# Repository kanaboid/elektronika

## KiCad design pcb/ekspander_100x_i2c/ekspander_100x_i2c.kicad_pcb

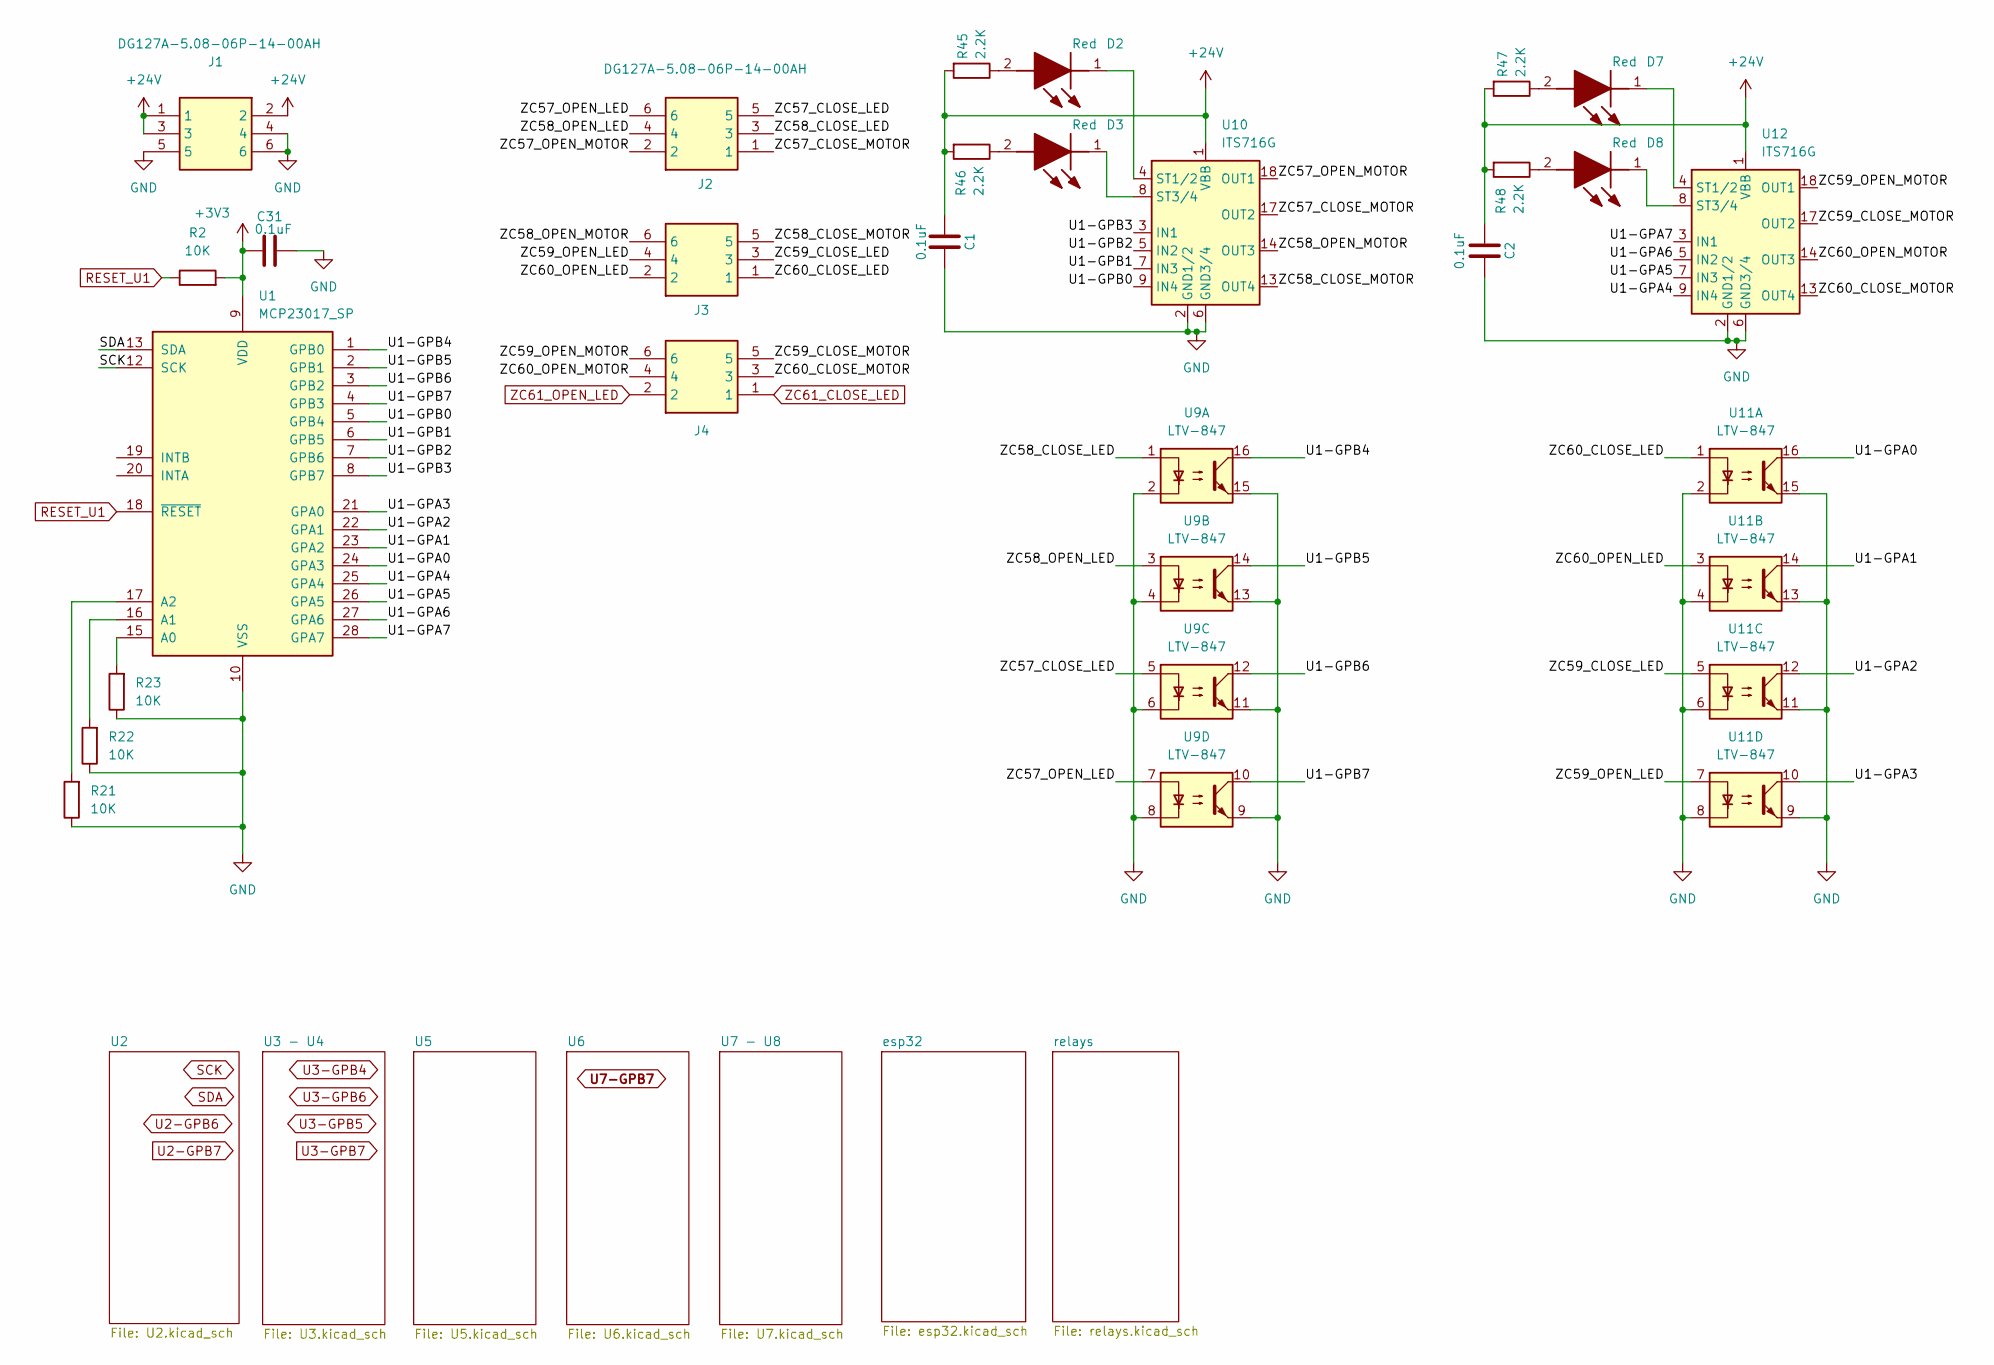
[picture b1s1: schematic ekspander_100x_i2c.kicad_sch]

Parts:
C1, C2, C31: 0.1uF; C_0805_2012Metric_Pad1.18x1.45mm_HandSolder
D2, D3, D7, D8: Red; LEDC2012X120N; Manufacturer_Part_Number LTST-C170KRKT; Mouser Part Number 859-LTST-C170KRKT
J1, J2, J3, J4: DG127A-5.08-06P-14-00AH; DG127A50806P1400AH; Manufacturer_Part_Number DG127A-5.08-06P-14-00AH
R2, R21, R22, R23: 10K; R_0805_2012Metric_Pad1.20x1.40mm_HandSolder
R45, R46, R47, R48: 2.2K; R_0805_2012Metric_Pad1.20x1.40mm_HandSolder
U1: MCP23017_SP; DIP-28_W7.62mm
U9, U11: LTV-847; DIP-16_W7.62mm
U10, U12: ITS716G; SOIC-20W_7.5x12.8mm_P1.27mm

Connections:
+3V3: C31.1, R2.2, U1.9 (VDD); also elsewhere on the board
+24V: C1.1, C2.1, J1.1, J1.2, J1.3, R45.2, R46.2, R47.2, R48.2, U10.1 (VBB), U10.10 (VBB), U10.11 (VBB), U10.12 (VBB), U10.15 (VBB), U10.16 (VBB), U10.19 (VBB), U10.20 (VBB), U12.1 (VBB), U12.10 (VBB), U12.11 (VBB), U12.12 (VBB), U12.15 (VBB), U12.16 (VBB), U12.19 (VBB), U12.20 (VBB); also elsewhere on the board
/U1-GPA0: U1.24 (GPA3), U11.16
/U1-GPA1: U1.23 (GPA2), U11.14
/U1-GPA2: U1.22 (GPA1), U11.12
/U1-GPA3: U1.21 (GPA0), U11.10
/U1-GPA4: U1.25 (GPA4), U12.9 (IN4)
/U1-GPA5: U1.26 (GPA5), U12.7 (IN3)
/U1-GPA6: U1.27 (GPA6), U12.5 (IN2)
/U1-GPA7: U1.28 (GPA7), U12.3 (IN1)
/U1-GPB0: U1.5 (GPB4), U10.9 (IN4)
/U1-GPB1: U1.6 (GPB5), U10.7 (IN3)
/U1-GPB2: U1.7 (GPB6), U10.5 (IN2)
/U1-GPB3: U1.8 (GPB7), U10.3 (IN1)
/U1-GPB4: U1.1 (GPB0), U9.16
/U1-GPB5: U1.2 (GPB1), U9.14
/U1-GPB6: U1.3 (GPB2), U9.12
/U1-GPB7: U1.4 (GPB3), U9.10
/ZC57_CLOSE_LED: J2.5, U9.5
/ZC57_CLOSE_MOTOR: J2.1, U10.17 (OUT2)
/ZC57_OPEN_LED: J2.6, U9.7
/ZC57_OPEN_MOTOR: J2.2, U10.18 (OUT1)
/ZC58_CLOSE_LED: J2.3, U9.1
/ZC58_CLOSE_MOTOR: J3.5, U10.13 (OUT4)
/ZC58_OPEN_LED: J2.4, U9.3
/ZC58_OPEN_MOTOR: J3.6, U10.14 (OUT3)
/ZC59_CLOSE_LED: J3.3, U11.5
/ZC59_CLOSE_MOTOR: J4.5, U12.17 (OUT2)
/ZC59_OPEN_LED: J3.4, U11.7
/ZC59_OPEN_MOTOR: J4.6, U12.18 (OUT1)
/ZC60_CLOSE_LED: J3.1, U11.1
/ZC60_CLOSE_MOTOR: J4.3, U12.13 (OUT4)
/ZC60_OPEN_LED: J3.2, U11.3
/ZC60_OPEN_MOTOR: J4.4, U12.14 (OUT3)
GND: C1.2, C2.2, C31.2, J1.4, J1.5, J1.6, R21.1, R22.1, R23.1, U1.10 (VSS), U9.2, U9.4, U9.6, U9.8, U9.9, U9.11, U9.13, U9.15, U10.2 (GND1/2), U10.6 (GND3/4), U11.2, U11.4, U11.6, U11.8, U11.9, U11.11, U11.13, U11.15, U12.2 (GND1/2), U12.6 (GND3/4); also elsewhere on the board
unnamed: D2.2 (A), R45.1
unnamed: D2.1 (K), U10.4 (ST1/2)
unnamed: D3.2 (A), R46.1
unnamed: D3.1 (K), U10.8 (ST3/4)
unnamed: D7.2 (A), R47.1
unnamed: D7.1 (K), U12.4 (ST1/2)
unnamed: D8.2 (A), R48.1
unnamed: D8.1 (K), U12.8 (ST3/4)
unnamed: R23.2, U1.15 (A0)
unnamed: R22.2, U1.16 (A1)
unnamed: R21.2, U1.17 (A2)
RESET_U1: R2.1, U1.18 (~RESET); also elsewhere on the board
SCK: U1.12 (SCK); also elsewhere on the board
SDA: U1.13 (SDA); also elsewhere on the board
ZC61_CLOSE_LED: J4.1; also elsewhere on the board
ZC61_OPEN_LED: J4.2; also elsewhere on the board

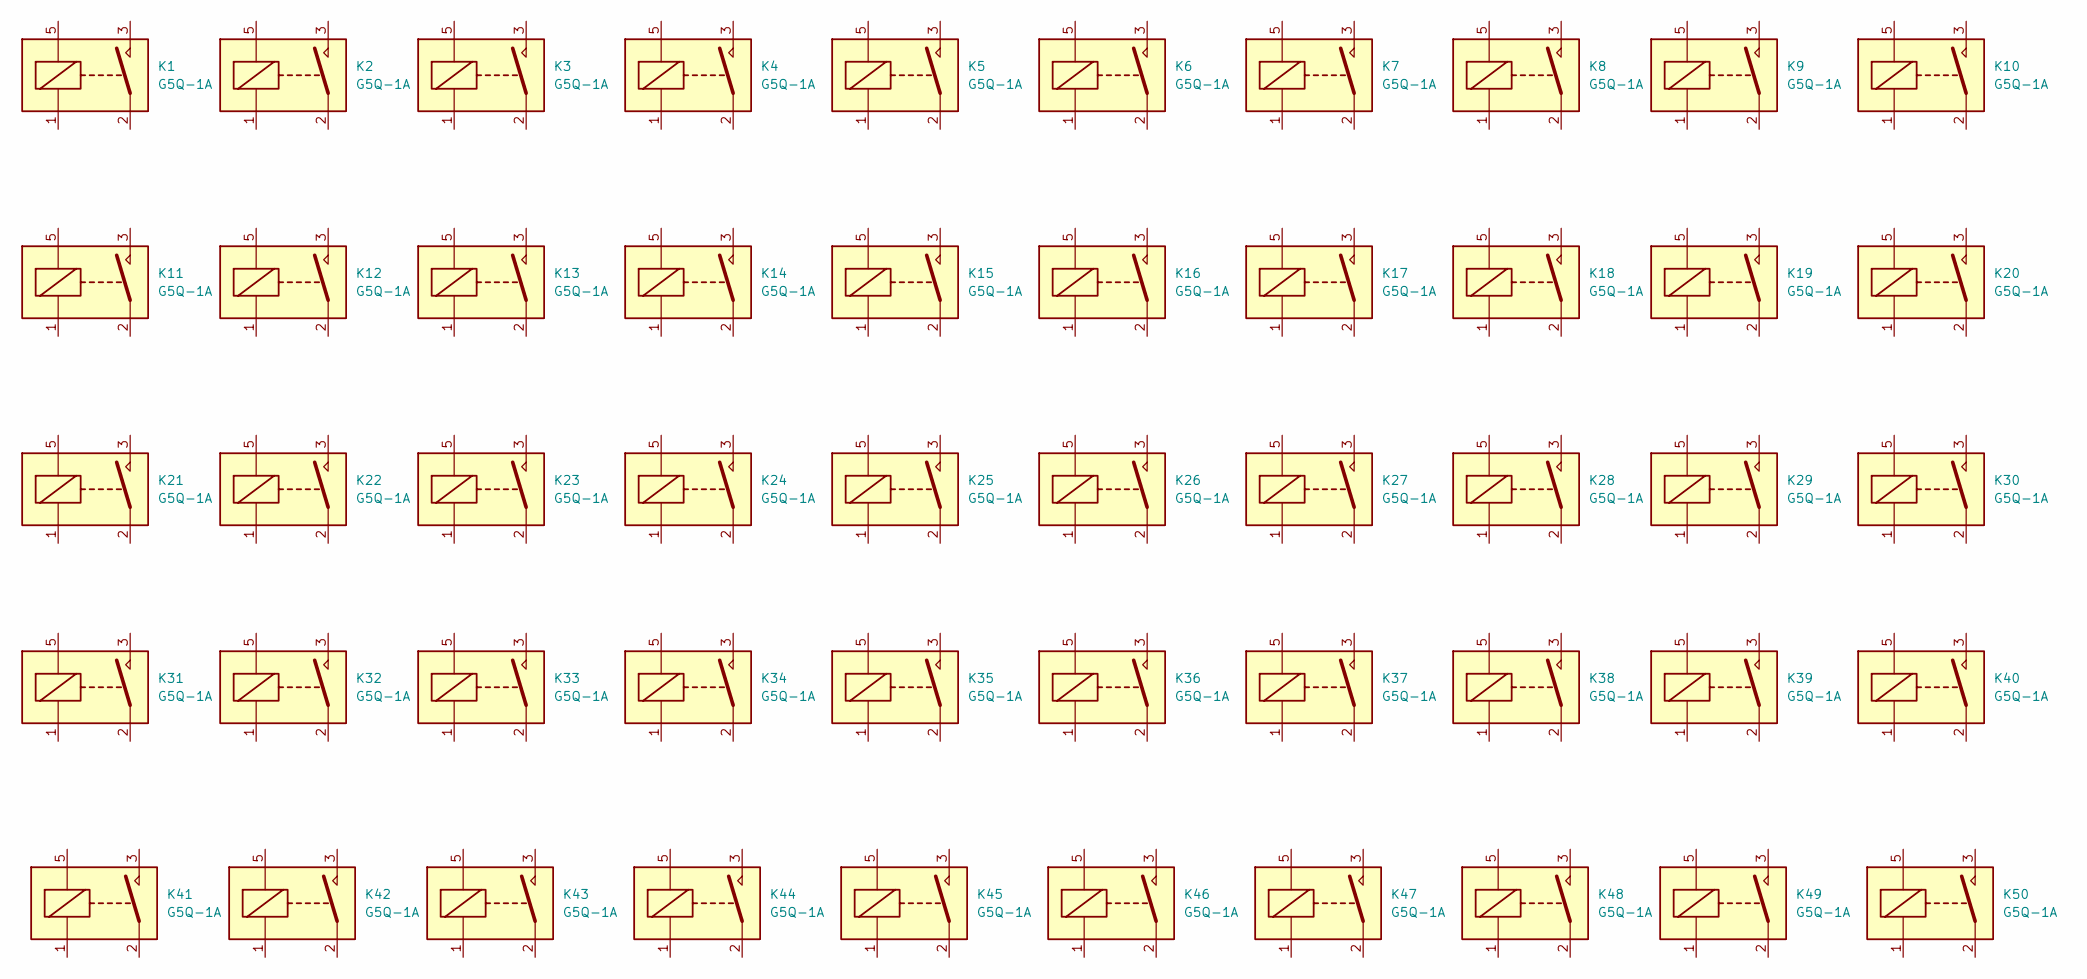
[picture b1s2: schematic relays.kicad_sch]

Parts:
K1, K2, K3, K4, K5, K6, K7, K8, K9, K10, K11, K12, K13, K14, K15, K16, K17, K18, K19, K20, K21, K22, K23, K24, K25, K26, K27, K28, K29, K30, K31, K32, K33, K34, K35, K36, K37, K38, K39, K40, K41, K42, K43, K44, K45, K46, K47, K48, K49, K50: G5Q-1A; Relay_SPST_Omron-G5Q-1A

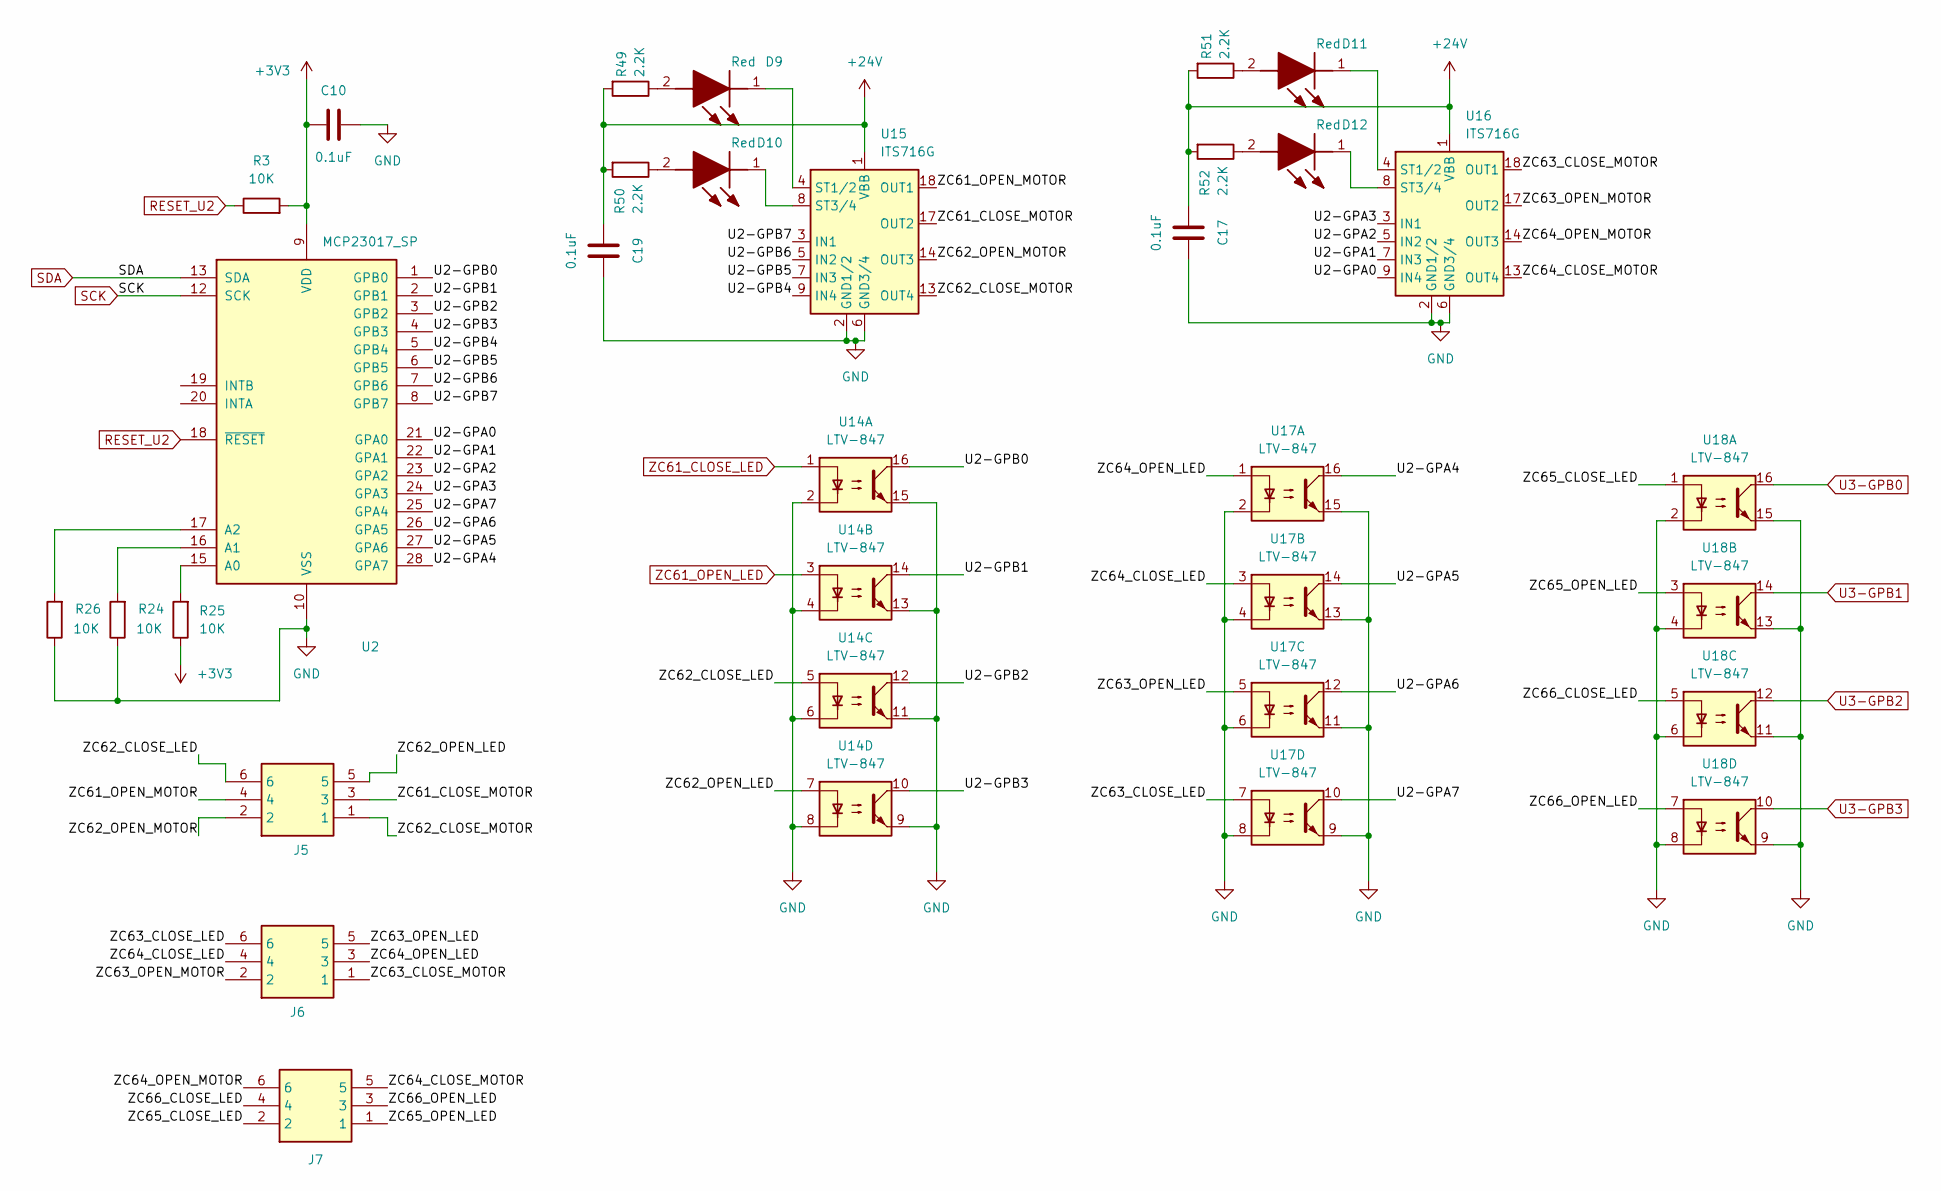
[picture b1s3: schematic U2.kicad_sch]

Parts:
C10, C17, C19: 0.1uF; C_0805_2012Metric_Pad1.18x1.45mm_HandSolder
D9, D10, D11, D12: Red; LEDC2012X120N; Manufacturer_Part_Number LTST-C170KRKT; Mouser Part Number 859-LTST-C170KRKT
J5, J6, J7: DG127A-5.08-06P-14-00AH; DG127A50806P1400AH; Manufacturer_Part_Number DG127A-5.08-06P-14-00AH
R3, R24, R25, R26: 10K; R_0805_2012Metric_Pad1.20x1.40mm_HandSolder
R49, R50, R51, R52: 2.2K; R_0805_2012Metric_Pad1.20x1.40mm_HandSolder
U2: MCP23017_SP; DIP-28_W7.62mm
U14, U17, U18: LTV-847; DIP-16_W7.62mm
U15, U16: ITS716G; SOIC-20W_7.5x12.8mm_P1.27mm

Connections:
+3V3: C10.1, R3.2, R25.1, U2.9 (VDD); also elsewhere on the board
+24V: C17.1, C19.1, R49.2, R50.2, R51.2, R52.2, U15.1 (VBB), U15.10 (VBB), U15.11 (VBB), U15.12 (VBB), U15.15 (VBB), U15.16 (VBB), U15.19 (VBB), U15.20 (VBB), U16.1 (VBB), U16.10 (VBB), U16.11 (VBB), U16.12 (VBB), U16.15 (VBB), U16.16 (VBB), U16.19 (VBB), U16.20 (VBB); also elsewhere on the board
/U2/U2-GPA0: U2.21 (GPA0), U16.9 (IN4)
/U2/U2-GPA1: U2.22 (GPA1), U16.7 (IN3)
/U2/U2-GPA2: U2.23 (GPA2), U16.5 (IN2)
/U2/U2-GPA3: U2.24 (GPA3), U16.3 (IN1)
/U2/U2-GPA4: U2.28 (GPA7), U17.16
/U2/U2-GPA5: U2.27 (GPA6), U17.14
/U2/U2-GPA6: U2.26 (GPA5), U17.12
/U2/U2-GPA7: U2.25 (GPA4), U17.10
/U2/U2-GPB0: U2.1 (GPB0), U14.16
/U2/U2-GPB1: U2.2 (GPB1), U14.14
/U2/U2-GPB2: U2.3 (GPB2), U14.12
/U2/U2-GPB3: U2.4 (GPB3), U14.10
/U2/U2-GPB4: U2.5 (GPB4), U15.9 (IN4)
/U2/U2-GPB5: U2.6 (GPB5), U15.7 (IN3)
/U2/U2-GPB6: U2.7 (GPB6), U15.5 (IN2)
/U2/U2-GPB7: U2.8 (GPB7), U15.3 (IN1)
/U2/ZC61_CLOSE_MOTOR: J5.3, U15.17 (OUT2)
/U2/ZC61_OPEN_MOTOR: J5.4, U15.18 (OUT1)
/U2/ZC62_CLOSE_LED: J5.6, U14.5
/U2/ZC62_CLOSE_MOTOR: J5.1, U15.13 (OUT4)
/U2/ZC62_OPEN_LED: J5.5, U14.7
/U2/ZC62_OPEN_MOTOR: J5.2, U15.14 (OUT3)
/U2/ZC63_CLOSE_LED: J6.6, U17.7
/U2/ZC63_CLOSE_MOTOR: J6.1, U16.18 (OUT1)
/U2/ZC63_OPEN_LED: J6.5, U17.5
/U2/ZC63_OPEN_MOTOR: J6.2, U16.17 (OUT2)
/U2/ZC64_CLOSE_LED: J6.4, U17.3
/U2/ZC64_CLOSE_MOTOR: J7.5, U16.13 (OUT4)
/U2/ZC64_OPEN_LED: J6.3, U17.1
/U2/ZC64_OPEN_MOTOR: J7.6, U16.14 (OUT3)
/U2/ZC65_CLOSE_LED: J7.2, U18.1
/U2/ZC65_OPEN_LED: J7.1, U18.3
/U2/ZC66_CLOSE_LED: J7.4, U18.5
/U2/ZC66_OPEN_LED: J7.3, U18.7
GND: C10.2, C17.2, C19.2, R24.1, R26.1, U2.10 (VSS), U14.2, U14.4, U14.6, U14.8, U14.9, U14.11, U14.13, U14.15, U15.2 (GND1/2), U15.6 (GND3/4), U16.2 (GND1/2), U16.6 (GND3/4), U17.2, U17.4, U17.6, U17.8, U17.9, U17.11, U17.13, U17.15, U18.2, U18.4, U18.6, U18.8, U18.9, U18.11, U18.13, U18.15; also elsewhere on the board
unnamed: D9.2 (A), R49.1
unnamed: D9.1 (K), U15.4 (ST1/2)
unnamed: D10.2 (A), R50.1
unnamed: D10.1 (K), U15.8 (ST3/4)
unnamed: D11.2 (A), R51.1
unnamed: D11.1 (K), U16.4 (ST1/2)
unnamed: D12.2 (A), R52.1
unnamed: D12.1 (K), U16.8 (ST3/4)
unnamed: R25.2, U2.15 (A0)
unnamed: R24.2, U2.16 (A1)
unnamed: R26.2, U2.17 (A2)
RESET_U2: R3.1, U2.18 (~RESET); also elsewhere on the board
SCK: U2.12 (SCK); also elsewhere on the board
SDA: U2.13 (SDA); also elsewhere on the board
U3-GPB0: U18.16; also elsewhere on the board
U3-GPB1: U18.14; also elsewhere on the board
U3-GPB2: U18.12; also elsewhere on the board
U3-GPB3: U18.10; also elsewhere on the board
ZC61_CLOSE_LED: U14.1; also elsewhere on the board
ZC61_OPEN_LED: U14.3; also elsewhere on the board

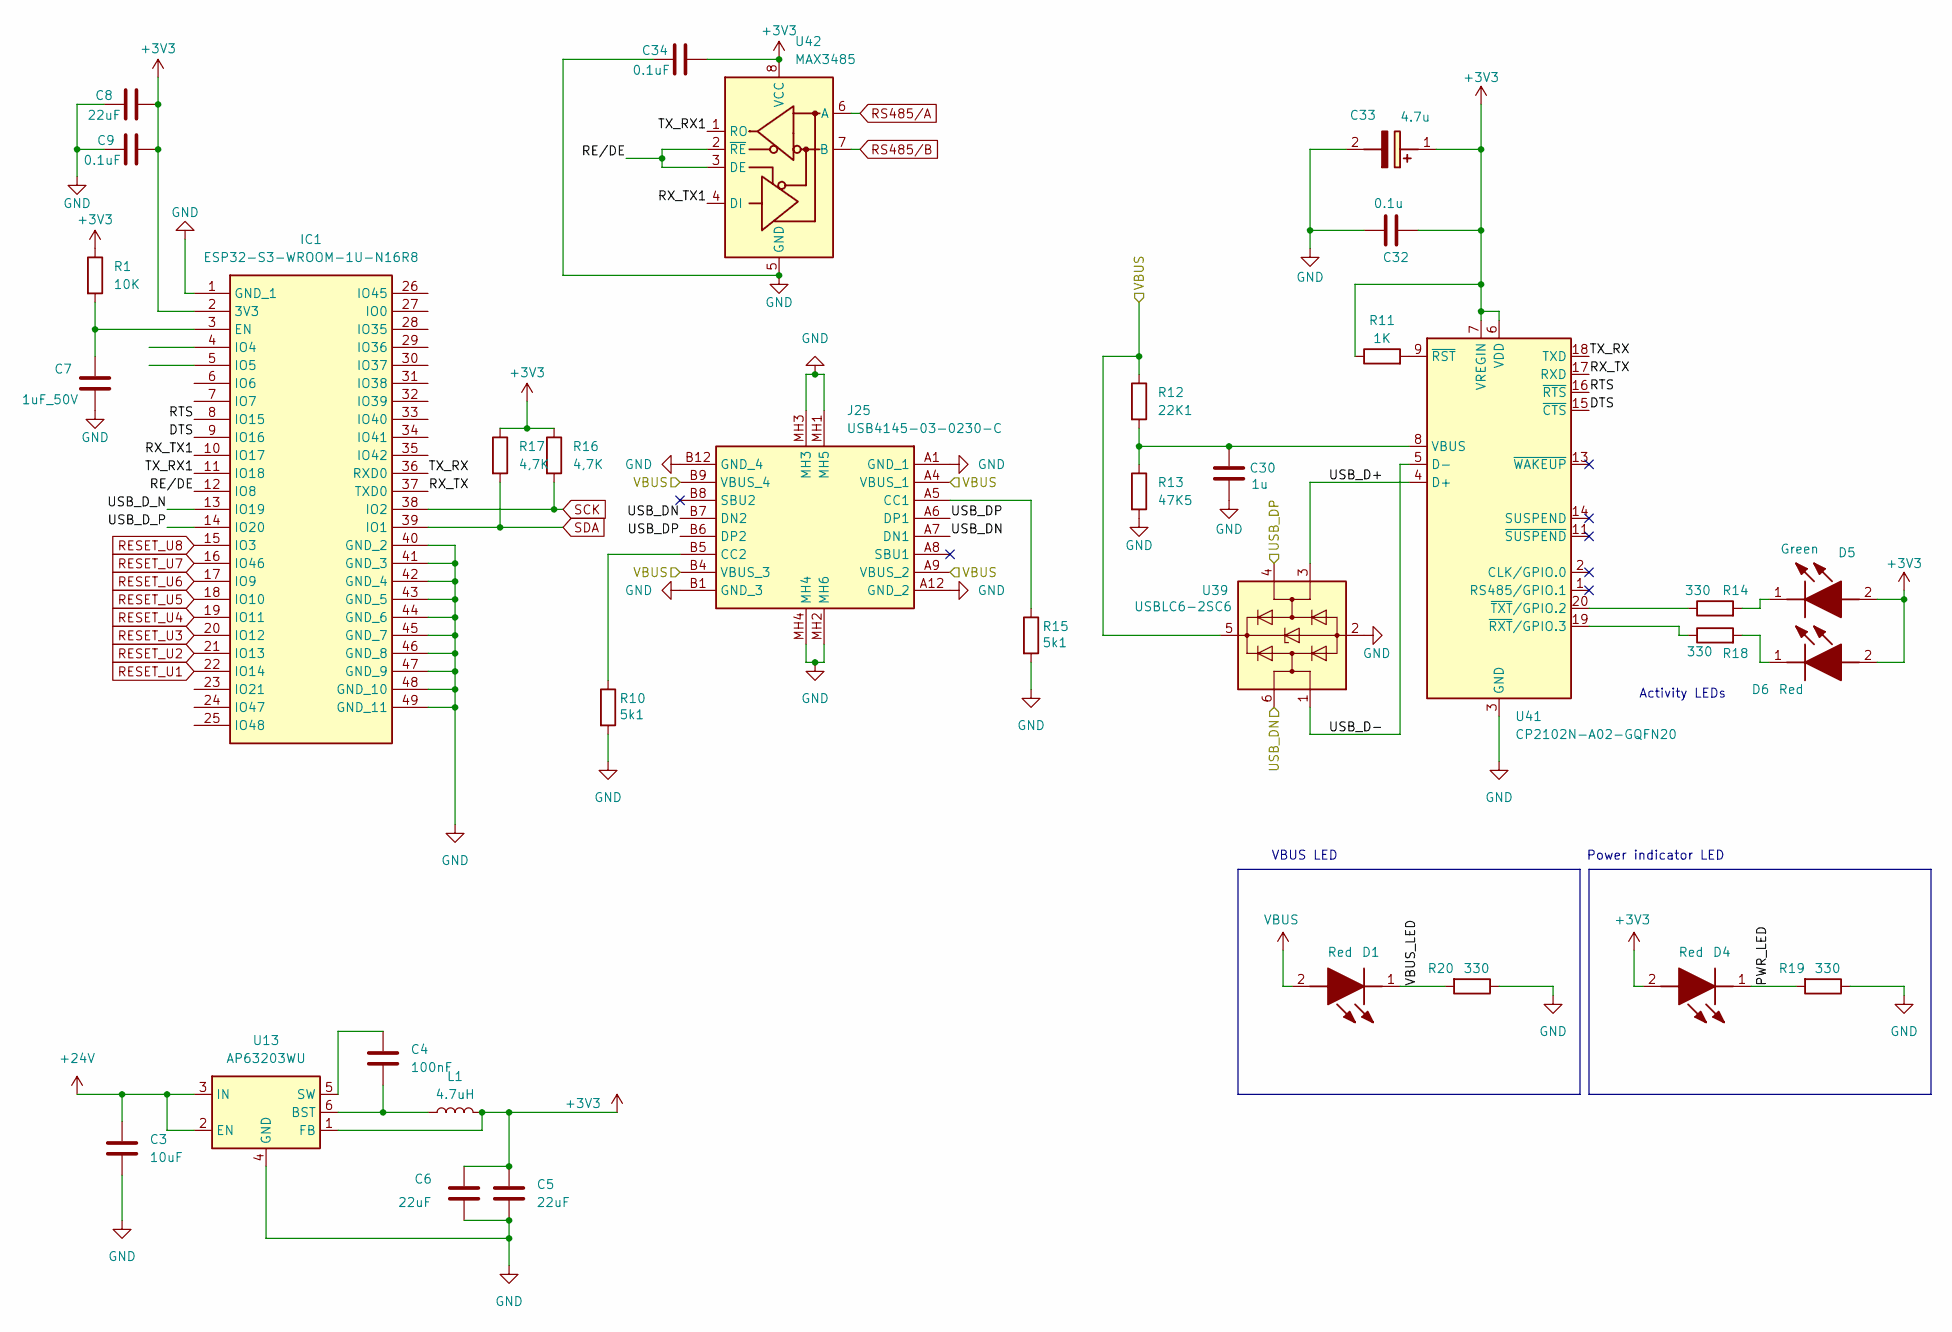
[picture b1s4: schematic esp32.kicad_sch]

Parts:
C3: 10uF; C_0805_2012Metric_Pad1.18x1.45mm_HandSolder
C4: 100nF; C_0805_2012Metric_Pad1.18x1.45mm_HandSolder
C5, C6, C8: 22uF; C_0805_2012Metric_Pad1.18x1.45mm_HandSolder
C7: 1uF_50V; C_0805_2012Metric_Pad1.18x1.45mm_HandSolder
C9, C34: 0.1uF; C_0805_2012Metric_Pad1.18x1.45mm_HandSolder
C30: 1u; C_0805_2012Metric; Voltage 1kV; Tolerance 100%
C32: 0.1u; C_0805_2012Metric; Voltage 1kV; Tolerance 100%
C33: 4.7u; T491A; Voltage 1kV; Tolerance 100%; Manufacturer_Part_Number T491A106K010AT7280; Mouser Part Number 80-T491A106K107280
D1, D4, D6: Red; LEDC2012X120N; Manufacturer_Part_Number LTST-C170KRKT; Mouser Part Number 859-LTST-C170KRKT
D5: Green; LEDC2012X120N; Manufacturer_Part_Number LTST-C170GKT; Mouser Part Number 859-LTST-C170GKT
IC1: ESP32-S3-WROOM-1U-N16R8; ESP32S3WROOM1UN16R8; Manufacturer_Part_Number ESP32-S3-WROOM-1U-N16R8
J25: USB4145-03-0230-C; USB4145030230C; Manufacturer_Part_Number USB4145-03-0230-C
L1: 4.7uH; LSXND6060YEL4R7NMG
R1: 10K; R_0805_2012Metric_Pad1.20x1.40mm_HandSolder
R10, R15: 5k1; R_0805_2012Metric
R11: 1K; R_0805_2012Metric
R12: 22K1; R_0805_2012Metric
R13: 47K5; R_0805_2012Metric
R14, R18, R19, R20: 330; R_0805_2012Metric
R16, R17: 4,7K; R_0805_2012Metric_Pad1.20x1.40mm_HandSolder
U13: AP63203WU; TSOT-23-6
U39: USBLC6-2SC6; SOT-23-6; Manufacturer_Part_Number USBLC6-2SC6; Mouser Part Number 511-USBLC6-2SC6
U41: CP2102N-A02-GQFN20; SiliconLabs_QFN-20-1EP_3x3mm_P0.5mm_EP1.8x1.8mm; Manufacturer_Part_Number CP2102N-A02-GQFN20
U42: MAX3485; SOIC-8_3.9x4.9mm_P1.27mm

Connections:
+3V3: C5.1, C6.1, C8.2, C9.2, C32.1, C33.1 (+), C34.2, D4.2 (A), D5.2 (A), D6.2 (A), IC1.2 (3V3), L1.2, R1.1, R11.1, R16.1, R17.1, U13.1 (FB), U41.6 (VDD), U41.7 (VREGIN), U42.8 (VCC); also elsewhere on the board
+24V: C3.1, U13.2 (EN), U13.3 (IN); also elsewhere on the board
/esp32/DTS: IC1.9 (IO16), U41.15 (~CTS)
/esp32/PWR_LED: D4.1 (K), R19.2
/esp32/RE/DE: IC1.12 (IO8), U42.2 (~RE), U42.3 (DE)
/esp32/RTS: IC1.8 (IO15), U41.16 (~RTS)
/esp32/RX_TX: IC1.37 (TXD0), U41.17 (RXD)
/esp32/RX_TX1: IC1.10 (IO17), U42.4 (DI)
/esp32/TX_RX: IC1.36 (RXD0), U41.18 (TXD)
/esp32/TX_RX1: IC1.11 (IO18), U42.1 (RO)
/esp32/USB_D+: U39.3 (I/O2), U41.4 (D+)
/esp32/USB_D-: U39.1 (I/O1), U41.5 (D-)
/esp32/USB_DN: J25.A7 (DN1), J25.B7 (DN2), U39.6 (I/O1)
/esp32/USB_DP: J25.A6 (DP1), J25.B6 (DP2), U39.4 (I/O2)
/esp32/USB_D_N: IC1.13 (IO19)
/esp32/USB_D_P: IC1.14 (IO20)
/esp32/VBUS_LED: D1.1 (K), R20.2
GND: C3.2, C5.2, C6.2, C7.2, C8.1, C9.1, C30.2, C32.2, C33.2 (-), C34.1, IC1.1 (GND_1), IC1.40 (GND_2), IC1.41 (GND_3), IC1.42 (GND_4), IC1.43 (GND_5), IC1.44 (GND_6), IC1.45 (GND_7), IC1.46 (GND_8), IC1.47 (GND_9), IC1.48 (GND_10), IC1.49 (GND_11), J25.A1 (GND_1), J25.A12 (GND_2), J25.B1 (GND_3), J25.B12 (GND_4), J25.MH1 (MH5), J25.MH2 (MH6), J25.MH3, J25.MH4, R10.2, R13.2, R15.2, R19.1, R20.1, U13.4 (GND), U39.2 (GND), U41.3 (GND), U41.12 (GND), U41.21 (GND), U42.5 (GND); also elsewhere on the board
unnamed: D5.1 (K), R14.2
unnamed: D6.1 (K), R18.2
unnamed 282: C7.1, IC1.3 (EN), R1.2; also elsewhere on the board
unnamed 283: IC1.27 (IO0); also elsewhere on the board
unnamed: J25.A5 (CC1), R15.1
unnamed: J25.B5 (CC2), R10.1
unnamed: C4.2, L1.1, U13.6 (BST)
unnamed: C4.1, U13.5 (SW)
unnamed: C30.1, R12.2, R13.1, U41.8 (VBUS)
unnamed: R11.2, U41.9 (~RST)
unnamed: R18.1, U41.19 (~RXT/GPIO.3)
unnamed: R14.1, U41.20 (~TXT/GPIO.2)
RESET_U1: IC1.22 (IO14); also elsewhere on the board
RESET_U2: IC1.21 (IO13); also elsewhere on the board
RESET_U3: IC1.20 (IO12); also elsewhere on the board
RESET_U4: IC1.19 (IO11); also elsewhere on the board
RESET_U5: IC1.18 (IO10); also elsewhere on the board
RESET_U6: IC1.17 (IO9); also elsewhere on the board
RESET_U7: IC1.23 (IO21); also elsewhere on the board
RESET_U8: IC1.15 (IO3); also elsewhere on the board
RS485/A: U42.6 (A); also elsewhere on the board
RS485/B: U42.7 (B); also elsewhere on the board
SCK: IC1.38 (IO2), R16.2; also elsewhere on the board
SDA: IC1.39 (IO1), R17.2; also elsewhere on the board
VBUS: D1.2 (A), J25.A4 (VBUS_1), J25.A9 (VBUS_2), J25.B4 (VBUS_3), J25.B9 (VBUS_4), R12.1, U39.5 (VBUS)

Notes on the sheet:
VBUS LED
Power indicator LED
Activity LEDs

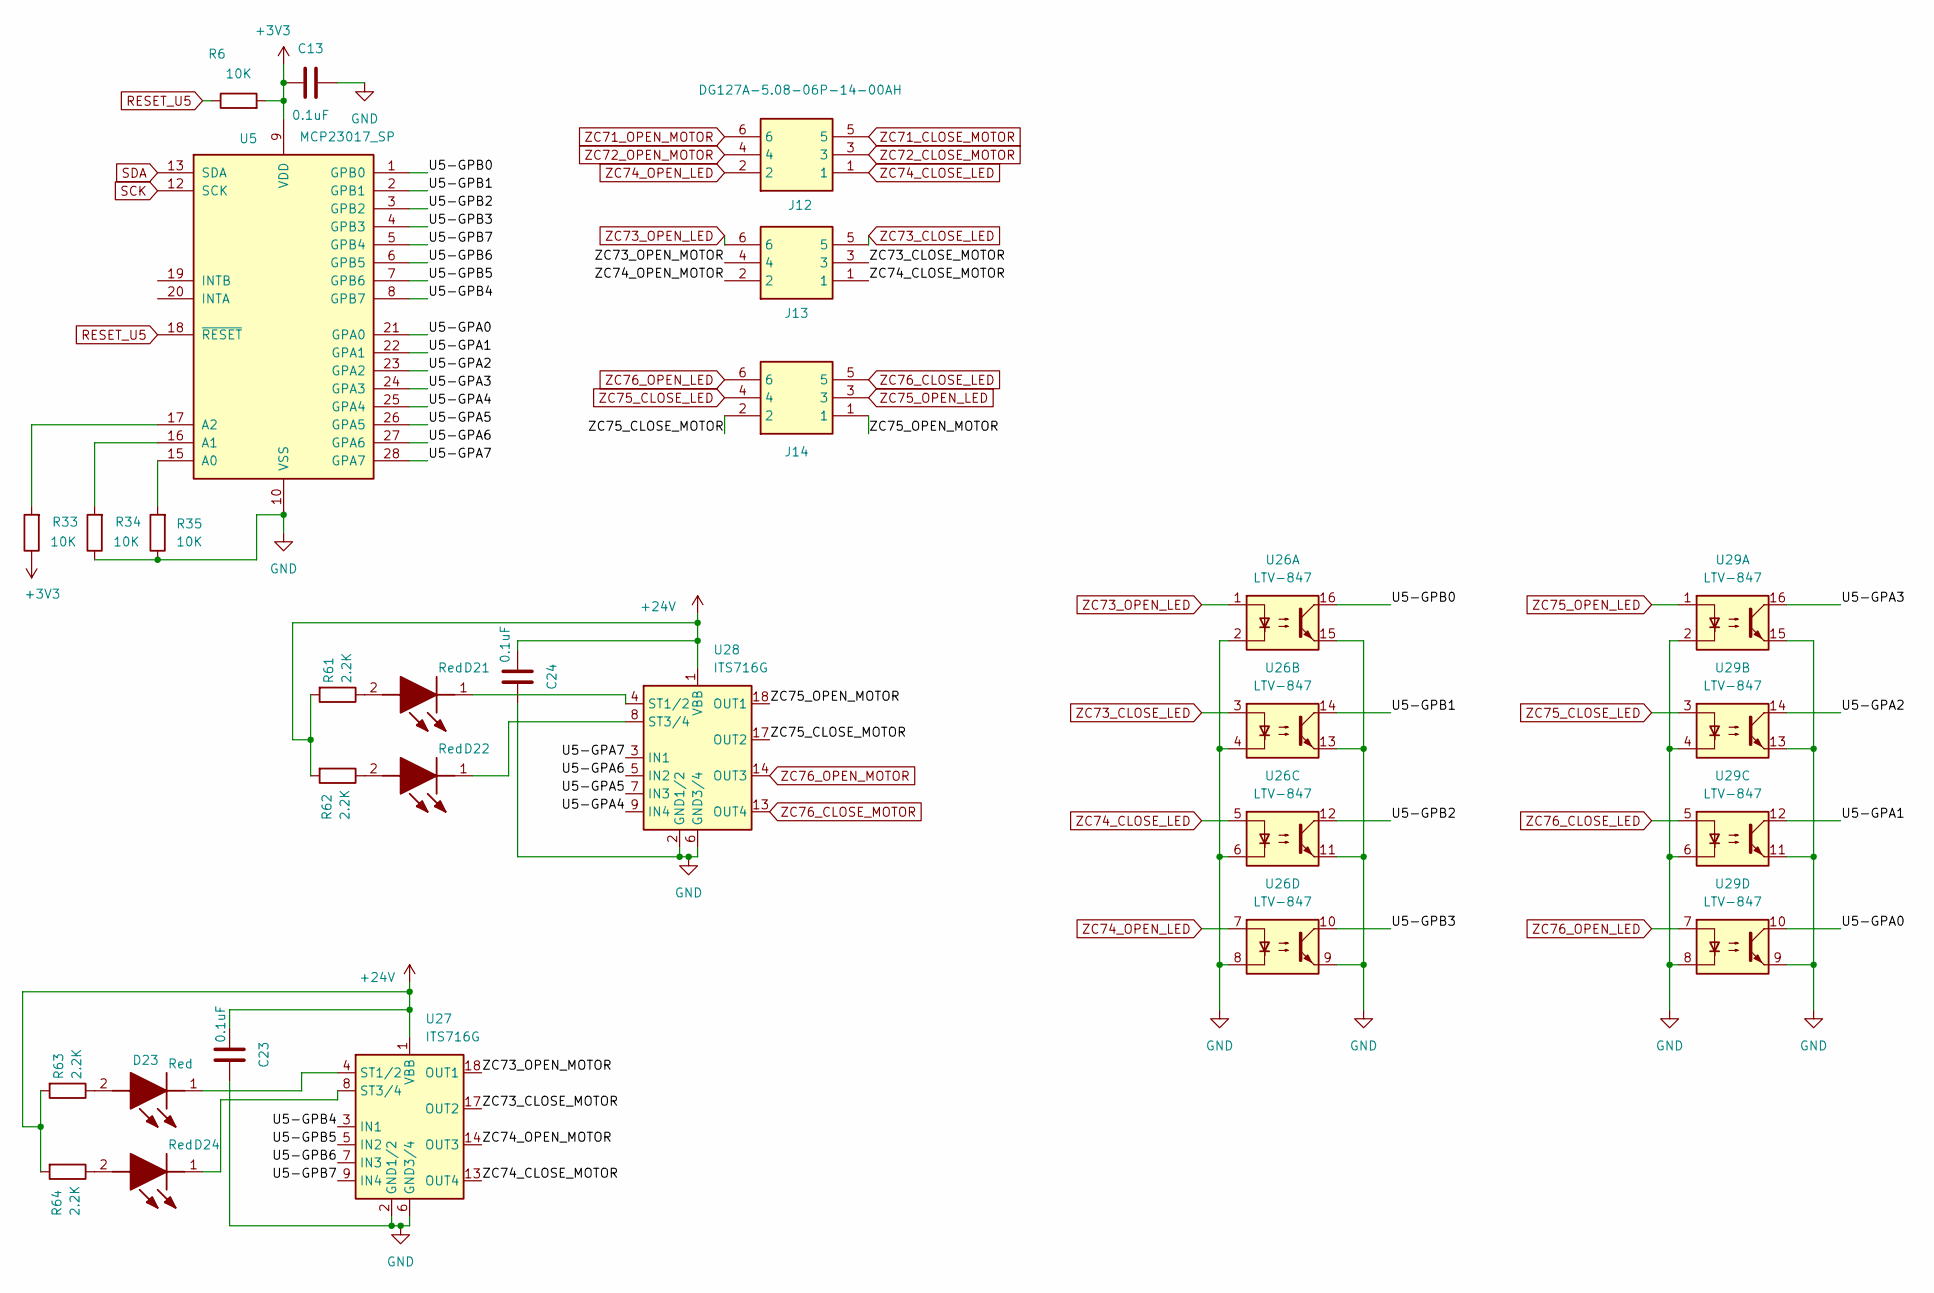
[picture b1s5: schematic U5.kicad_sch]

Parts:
C13, C23, C24: 0.1uF; C_0805_2012Metric_Pad1.18x1.45mm_HandSolder
D21, D22, D23, D24: Red; LEDC2012X120N; Manufacturer_Part_Number LTST-C170KRKT; Mouser Part Number 859-LTST-C170KRKT
J12, J13, J14: DG127A-5.08-06P-14-00AH; DG127A50806P1400AH; Manufacturer_Part_Number DG127A-5.08-06P-14-00AH
R6, R33, R34, R35: 10K; R_0805_2012Metric_Pad1.20x1.40mm_HandSolder
R61, R62, R63, R64: 2.2K; R_0805_2012Metric_Pad1.20x1.40mm_HandSolder
U5: MCP23017_SP; DIP-28_W7.62mm
U26, U29: LTV-847; DIP-16_W7.62mm
U27, U28: ITS716G; SOIC-20W_7.5x12.8mm_P1.27mm

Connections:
+3V3: C13.1, R6.2, R33.1, U5.9 (VDD); also elsewhere on the board
+24V: C23.1, C24.1, R61.2, R62.2, R63.2, R64.2, U27.1 (VBB), U27.10 (VBB), U27.11 (VBB), U27.12 (VBB), U27.15 (VBB), U27.16 (VBB), U27.19 (VBB), U27.20 (VBB), U28.1 (VBB), U28.10 (VBB), U28.11 (VBB), U28.12 (VBB), U28.15 (VBB), U28.16 (VBB), U28.19 (VBB), U28.20 (VBB); also elsewhere on the board
/U5/U5-GPA0: U5.21 (GPA0), U29.10
/U5/U5-GPA1: U5.22 (GPA1), U29.12
/U5/U5-GPA2: U5.23 (GPA2), U29.14
/U5/U5-GPA3: U5.24 (GPA3), U29.16
/U5/U5-GPA4: U5.25 (GPA4), U28.9 (IN4)
/U5/U5-GPA5: U5.26 (GPA5), U28.7 (IN3)
/U5/U5-GPA6: U5.27 (GPA6), U28.5 (IN2)
/U5/U5-GPA7: U5.28 (GPA7), U28.3 (IN1)
/U5/U5-GPB0: U5.1 (GPB0), U26.16
/U5/U5-GPB1: U5.2 (GPB1), U26.14
/U5/U5-GPB2: U5.3 (GPB2), U26.12
/U5/U5-GPB3: U5.4 (GPB3), U26.10
/U5/U5-GPB4: U5.8 (GPB7), U27.3 (IN1)
/U5/U5-GPB5: U5.7 (GPB6), U27.5 (IN2)
/U5/U5-GPB6: U5.6 (GPB5), U27.7 (IN3)
/U5/U5-GPB7: U5.5 (GPB4), U27.9 (IN4)
/U5/ZC73_CLOSE_MOTOR: J13.3, U27.17 (OUT2)
/U5/ZC73_OPEN_MOTOR: J13.4, U27.18 (OUT1)
/U5/ZC74_CLOSE_MOTOR: J13.1, U27.13 (OUT4)
/U5/ZC74_OPEN_MOTOR: J13.2, U27.14 (OUT3)
/U5/ZC75_CLOSE_MOTOR: J14.2, U28.17 (OUT2)
/U5/ZC75_OPEN_MOTOR: J14.1, U28.18 (OUT1)
GND: C13.2, C23.2, C24.2, R34.1, R35.1, U5.10 (VSS), U26.2, U26.4, U26.6, U26.8, U26.9, U26.11, U26.13, U26.15, U27.2 (GND1/2), U27.6 (GND3/4), U28.2 (GND1/2), U28.6 (GND3/4), U29.2, U29.4, U29.6, U29.8, U29.9, U29.11, U29.13, U29.15; also elsewhere on the board
unnamed: D21.2 (A), R61.1
unnamed: D21.1 (K), U28.4 (ST1/2)
unnamed: D22.2 (A), R62.1
unnamed: D22.1 (K), U28.8 (ST3/4)
unnamed: D23.2 (A), R63.1
unnamed: D23.1 (K), U27.4 (ST1/2)
unnamed: D24.2 (A), R64.1
unnamed: D24.1 (K), U27.8 (ST3/4)
unnamed: R35.2, U5.15 (A0)
unnamed: R34.2, U5.16 (A1)
unnamed: R33.2, U5.17 (A2)
RESET_U5: R6.1, U5.18 (~RESET); also elsewhere on the board
SCK: U5.12 (SCK); also elsewhere on the board
SDA: U5.13 (SDA); also elsewhere on the board
ZC71_CLOSE_MOTOR: J12.5; also elsewhere on the board
ZC71_OPEN_MOTOR: J12.6; also elsewhere on the board
ZC72_CLOSE_MOTOR: J12.3; also elsewhere on the board
ZC72_OPEN_MOTOR: J12.4; also elsewhere on the board
ZC73_CLOSE_LED: J13.5, U26.3
ZC73_OPEN_LED: J13.6, U26.1
ZC74_CLOSE_LED: J12.1, U26.5
ZC74_OPEN_LED: J12.2, U26.7
ZC75_CLOSE_LED: J14.4, U29.3
ZC75_OPEN_LED: J14.3, U29.1
ZC76_CLOSE_LED: J14.5, U29.5
ZC76_CLOSE_MOTOR: U28.13 (OUT4); also elsewhere on the board
ZC76_OPEN_LED: J14.6, U29.7
ZC76_OPEN_MOTOR: U28.14 (OUT3); also elsewhere on the board
